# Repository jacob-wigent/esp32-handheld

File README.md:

# ESP32-S3 Handheld Game Console
Handheld game console powered by an ESP32-S3, featuring a custom LED matrix display and a variety of inputs.

ESP32-S3
2020 NeoPixels (WS2812B)

10/10
- added through-hole power JST connector on display board

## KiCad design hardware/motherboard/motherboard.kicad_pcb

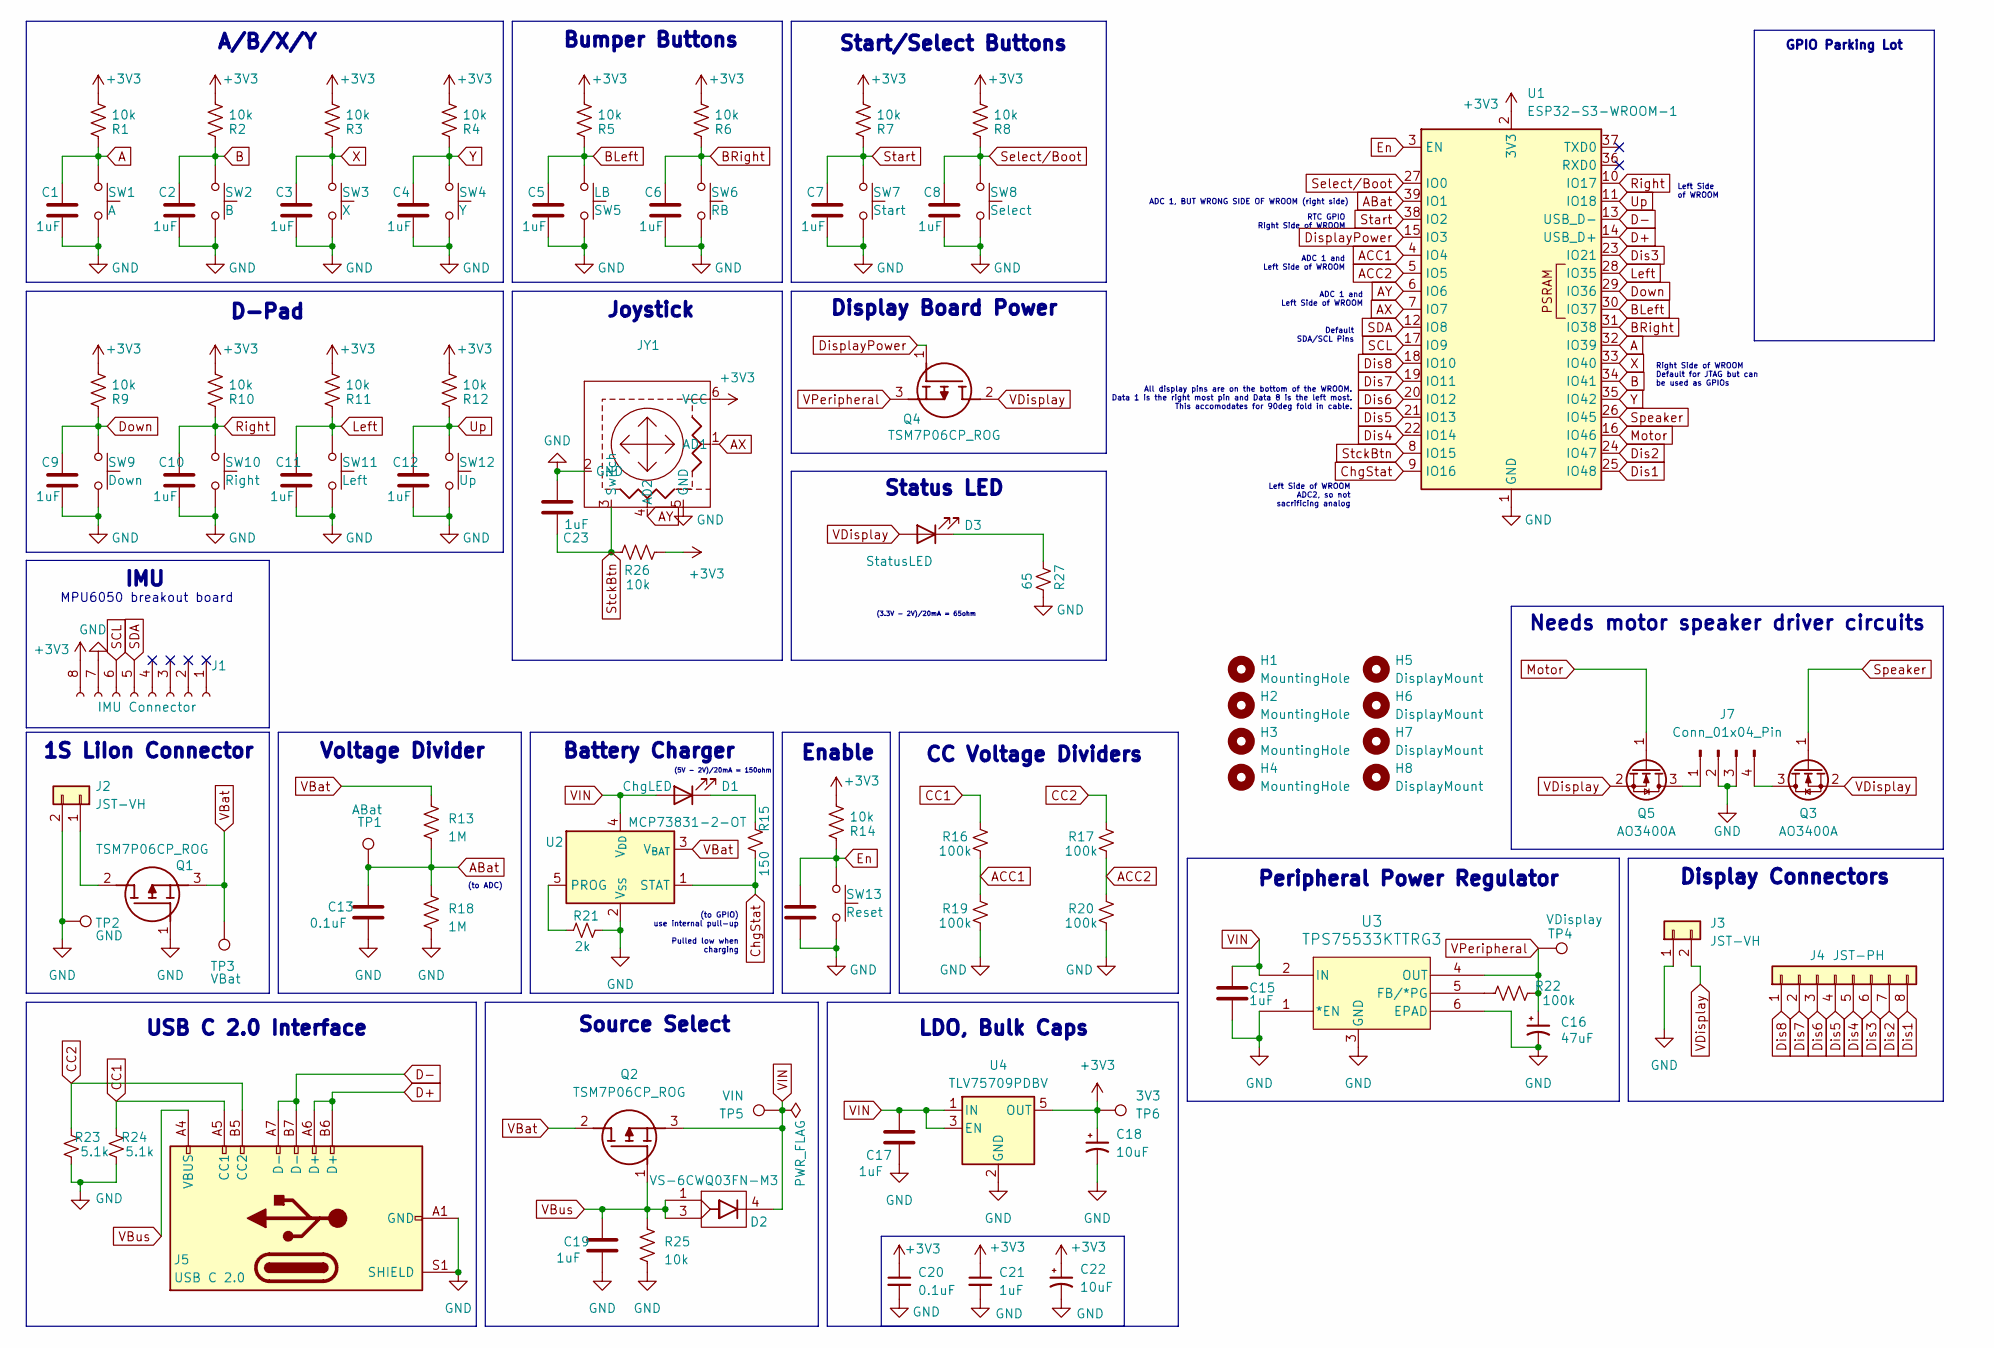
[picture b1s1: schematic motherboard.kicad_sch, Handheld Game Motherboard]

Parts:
C1, C2, C3, C4, C5, C6, C7, C8, C9, C10, C11, C12, C14, C15, C17, C19, C21, C23: 1uF; C_0805_2012Metric_Pad1.18x1.45mm_HandSolder
C13, C20: 0.1uF; C_0805_2012Metric_Pad1.18x1.45mm_HandSolder
C16: 47uF; CP_EIA-7343-31_Kemet-D
C18, C22: 10uF; C_0805_2012Metric_Pad1.18x1.45mm_HandSolder
D1: ChgLED; LED_1206_3216Metric_Pad1.42x1.75mm_HandSolder
D2: VS-6CWQ03FN-M3; DPAK_Q03FN-M3_VIS; Mouser Part Number 78-VS-6CWQ03FN-M3
D3: StatusLED; LED_1206_3216Metric_Pad1.42x1.75mm_HandSolder
H1, H2, H3, H4: MountingHole; MountingHole_3.2mm_M3_Pad
H5, H6, H7, H8: DisplayMount; MountingHole_3.2mm_M3_Pad
J1: IMU Connector; PinHeader_1x08_P2.54mm_Vertical
J2, J3: JST-VH; JST_VH_B2PS-VH_1x02_P3.96mm_Horizontal
J4: JST-PH; JST_PH_S8B-PH-K_1x08_P2.00mm_Horizontal
J5: USB C 2.0; USB_C_Receptacle_G-Switch_GT-USB-7010ASV
J7: Conn_01x04_Pin; JST_PH_S4B-PH-K_1x04_P2.00mm_Horizontal
JY1: Adafruit_Joycon
Q1, Q2, Q4: TSM7P06CP_ROG; TRANS_TSM7P06CP_ROG; Mouser Part Number 821-TSM7P06CPROG
Q3, Q5: AO3400A; SOT-23
R1, R2, R3, R4, R5, R6, R7, R8, R9, R10, R11, R12, R14, R25, R26: 10k; R_0805_2012Metric_Pad1.20x1.40mm_HandSolder
R13, R18: 1M; R_0805_2012Metric_Pad1.20x1.40mm_HandSolder
R15: 150; R_0805_2012Metric_Pad1.20x1.40mm_HandSolder
R16, R17, R19, R20, R22: 100k; R_0805_2012Metric_Pad1.20x1.40mm_HandSolder
R21: 2k; R_0805_2012Metric_Pad1.20x1.40mm_HandSolder
R23, R24: 5.1k; R_0805_2012Metric_Pad1.20x1.40mm_HandSolder
R27: 65; R_0805_2012Metric_Pad1.20x1.40mm_HandSolder
SW1: A; SW_PUSH_6mm
SW2: B; SW_PUSH_6mm
SW3: X; SW_PUSH_6mm
SW4: Y; SW_PUSH_6mm
SW5: LB; SW_Tactile_SPST_Angled_PTS645Vx58-2LFS
SW6: RB; SW_Tactile_SPST_Angled_PTS645Vx58-2LFS
SW7: Start; SW_PUSH_6mm
SW8: Select; SW_PUSH_6mm
SW9: Down; SW_PUSH_6mm
SW10: Right; SW_PUSH_6mm
SW11: Left; SW_PUSH_6mm
SW12: Up; SW_PUSH_6mm
SW13: Reset; SW_SPST_CK_RS282G05A3
TP1: ABat; TestPoint_Pad_D1.5mm
TP2: GND; TestPoint_Pad_D1.5mm
TP3: VBat; TestPoint_Pad_D1.5mm
TP4: VDisplay; TestPoint_Pad_D1.5mm
TP5: VIN; TestPoint_Pad_D1.5mm
TP6: 3V3; TestPoint_Pad_D1.5mm
U1: ESP32-S3-WROOM-1
U2: MCP73831-2-OT; SOT-23-5
U3: TPS75533KTTRG3; KTT5_6P22X6P86
U4: TLV75709PDBV; SOT-23-5

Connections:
+3V3: C18.1, C20.1, C21.1, C22.1, J1.8, JY1.6 (VCC), R1.2, R2.2, R3.2, R4.2, R5.2, R6.2, R7.2, R8.2, R9.2, R10.2, R11.2, R12.2, R14.2, R26.1, TP6.1, U1.2 (3V3), U4.5 (OUT)
A: C1.1, R1.1, SW1.1, U1.32 (IO39)
ABat: C13.1, R13.2, R18.1, TP1.1, U1.39 (IO1)
ACC1: R16.1, R19.2, U1.4 (IO4)
ACC2: R17.1, R20.2, U1.5 (IO5)
AX: JY1.1 (AD1), U1.7 (IO7)
AY: JY1.4 (AD2), U1.6 (IO6)
B: C2.1, R2.1, SW2.1, U1.34 (IO41)
BLeft: C5.1, R5.1, SW5.2, U1.30 (IO37)
BRight: C6.1, R6.1, SW6.1, U1.31 (IO38)
CC1: J5.A5 (CC1), R16.2, R24.2
CC2: J5.B5 (CC2), R17.2, R23.2
ChgStat: R15.1, U1.9 (IO16), U2.1 (STAT)
D+: J5.A6 (D+), J5.B6 (D+), U1.14 (USB_D+)
D-: J5.A7 (D-), J5.B7 (D-), U1.13 (USB_D-)
Dis1: J4.8, U1.25 (IO48)
Dis2: J4.7, U1.24 (IO47)
Dis3: J4.6, U1.23 (IO21)
Dis4: J4.5, U1.22 (IO14)
Dis5: J4.4, U1.21 (IO13)
Dis6: J4.3, U1.20 (IO12)
Dis7: J4.2, U1.19 (IO11)
Dis8: J4.1, U1.18 (IO10)
Down: C9.1, R9.1, SW9.1, U1.29 (IO36)
En: C14.1, R14.1, SW13.1, U1.3 (EN)
Left: C11.1, R11.1, SW11.1, U1.28 (IO35)
Motor: Q5.1 (G), U1.16 (IO46)
unnamed: D1.1 (K), R15.2
unnamed: D3.1 (K), R27.2
unnamed: J2.1, Q1.2 (D)
unnamed 30: J7.1, Q5.3 (D); also elsewhere on the board
unnamed 31: J7.4, Q3.3 (D); also elsewhere on the board
unnamed: R21.1, U2.5 (PROG)
unnamed: R22.1, U3.5 (FB/*PG)
Right: C10.1, R10.1, SW10.1, U1.10 (IO17)
SCL: J1.6, U1.17 (IO9)
SDA: J1.5, U1.12 (IO8)
Select/Boot: C8.1, R8.1, SW8.1, U1.27 (IO0)
Speaker: Q3.1 (G), U1.26 (IO45)
Start: C7.1, R7.1, SW7.1, U1.38 (IO2)
StckBtn: C23.2, JY1.3 (Switch), R26.2, U1.8 (IO15)
Up: C12.1, R12.1, SW12.1, U1.11 (IO18)
VBat: Q1.3 (S), Q2.2 (D), R13.1, TP3.1, U2.3 (V_{BAT})
VBus: C19.1, D2.1, D2.3, J5.A4 (VBUS), J5.A9 (VBUS), J5.B4 (VBUS), J5.B9 (VBUS), Q2.1 (G), R25.1
VIN: C15.1, C17.1, D1.2 (A), D2.4, Q2.3 (S), TP5.1, U2.4 (V_{DD}), U3.2 (IN), U4.1 (IN), U4.3 (EN)
X: C3.1, R3.1, SW3.1, U1.33 (IO40)
Y: C4.1, R4.1, SW4.1, U1.35 (IO42)

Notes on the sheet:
(to GPIO) use internal pull-up Pulled low when charging
LDO, Bulk Caps
Left Side of WROOM
Bumper Buttons
Needs motor speaker driver circuits
Display Connectors
ADC 1 and Left Side of WROOM
Start/Select Buttons
USB C 2.0 Interface
1S LiIon Connector
CC Voltage Dividers
Right Side of WROOM Default for JTAG but can be used as GPIOs
Peripheral Power Regulator
Voltage Divider
D-Pad
(5V - 2V)/20mA = 150ohm
Source Select
IMU
(3.3V - 2V)/20mA = 65ohm
A/B/X/Y
All display pins are on the bottom of the WROOM. Data 1 is the right most pin and Data 8 is the left most. This accomodates for 90deg fold in cable.
MPU6050 breakout board
ADC 1, BUT WRONG SIDE OF WROOM (right side)
RTC GPIO Right Side of WROOM
Enable
Battery Charger
Joystick
Status LED
GPIO Parking Lot
Left Side of WROOM ADC2, so not sacrificing analog
(to ADC)
Default SDA/SCL Pins
Display Board Power

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
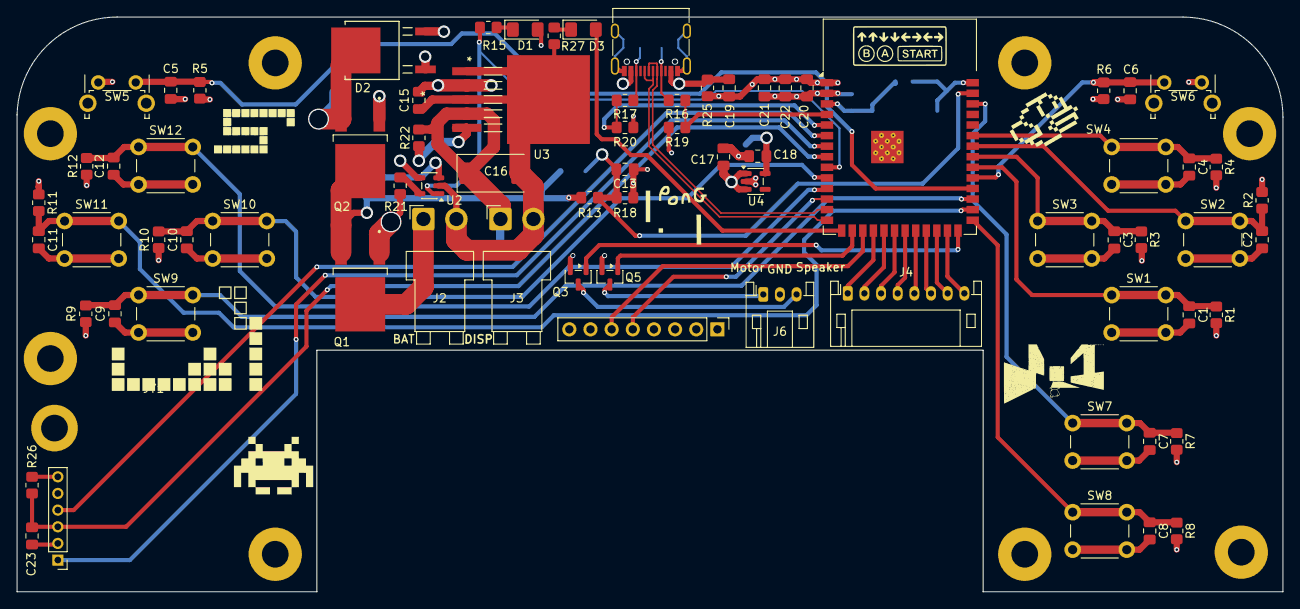
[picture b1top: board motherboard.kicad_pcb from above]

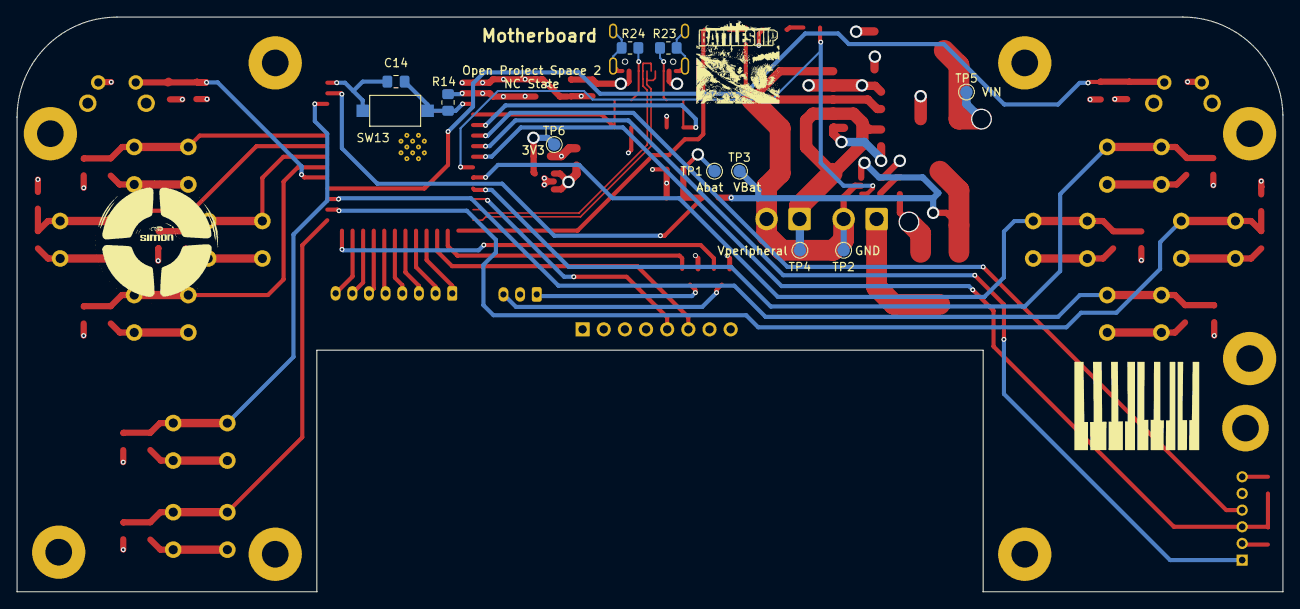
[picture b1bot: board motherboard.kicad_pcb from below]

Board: 4 copper layers, 152.0 x 69.0 mm, 95 parts (11 on the bottom side), 50 nets.

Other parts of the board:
J6: Conn_01x03_Pin; JST_PH_S3B-PH-K_1x03_P2.00mm_Horizontal

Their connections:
unnamed 30: J6.1; also elsewhere on the board
unnamed 31: J6.3; also elsewhere on the board

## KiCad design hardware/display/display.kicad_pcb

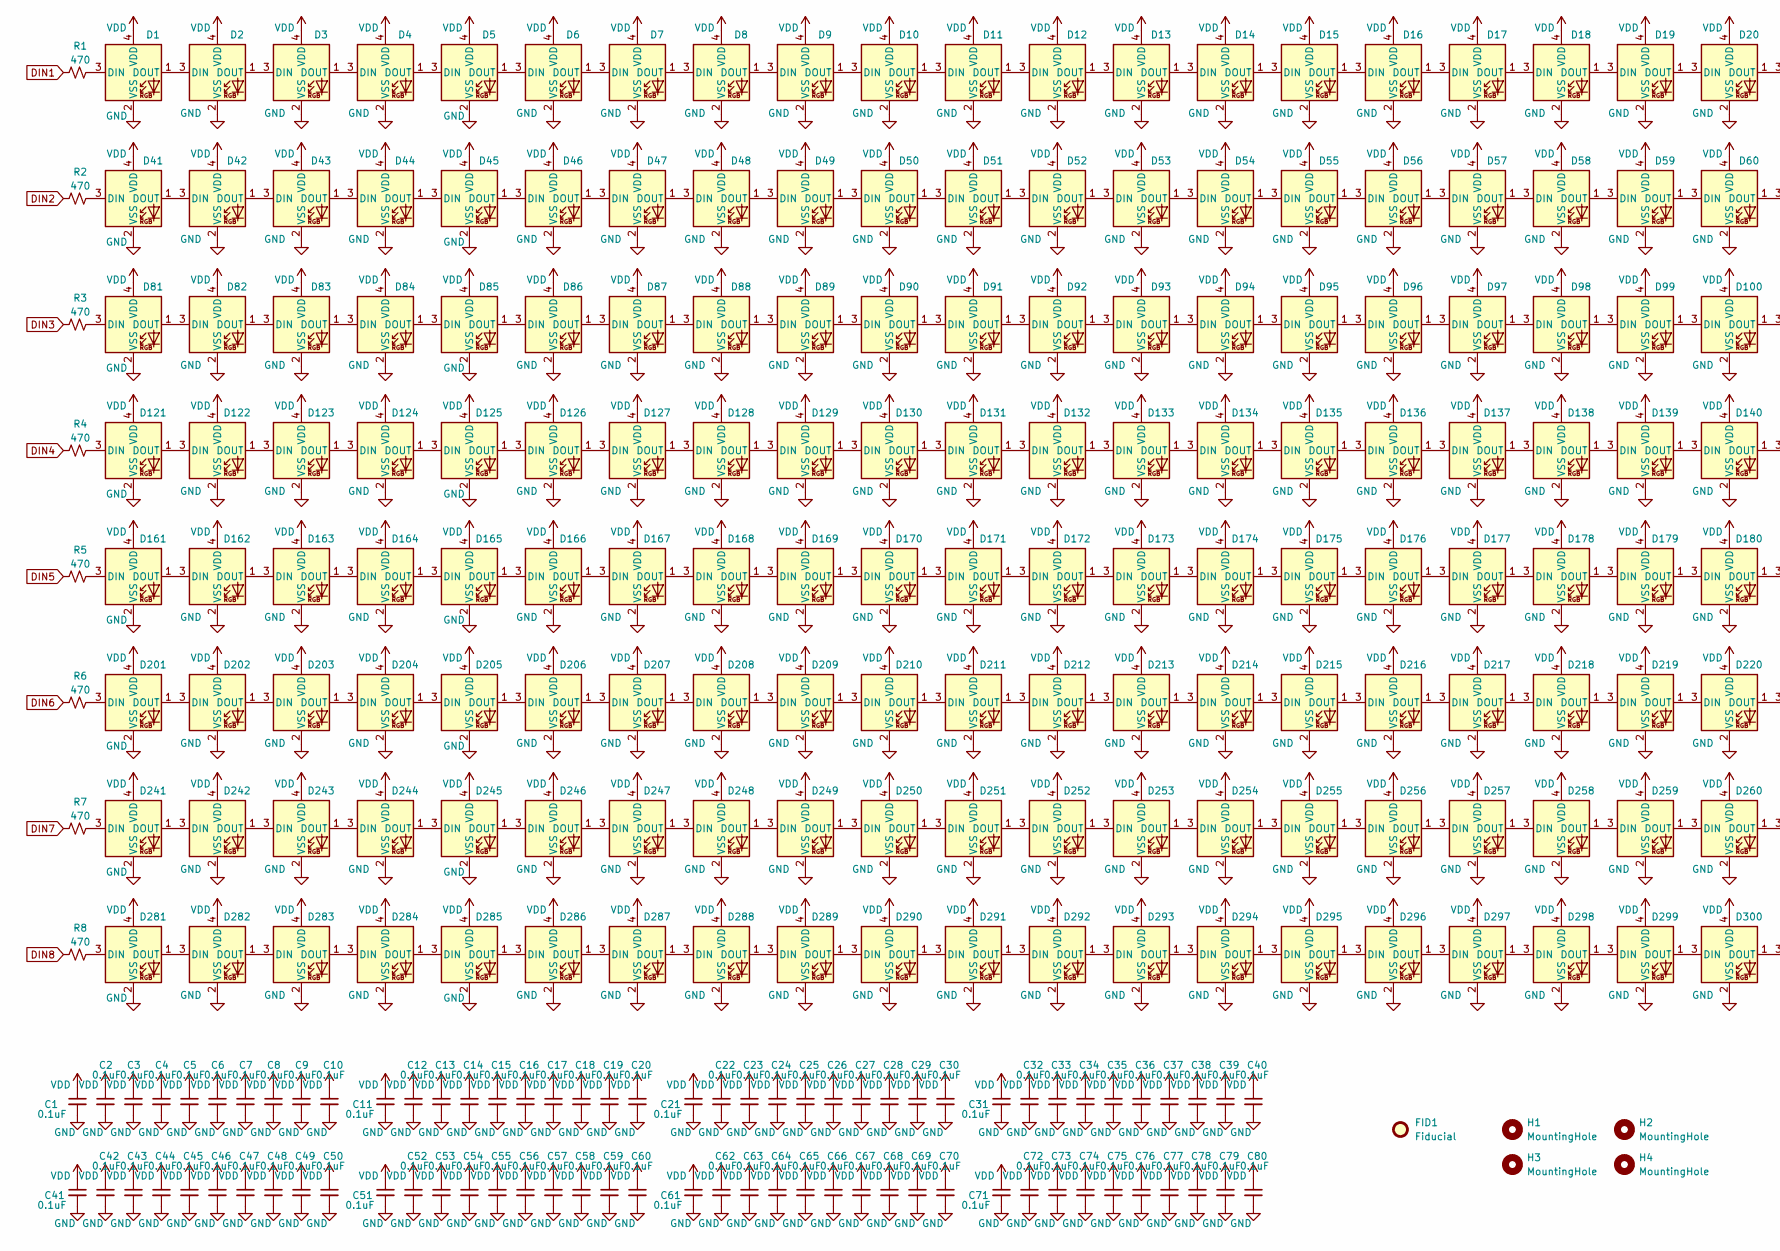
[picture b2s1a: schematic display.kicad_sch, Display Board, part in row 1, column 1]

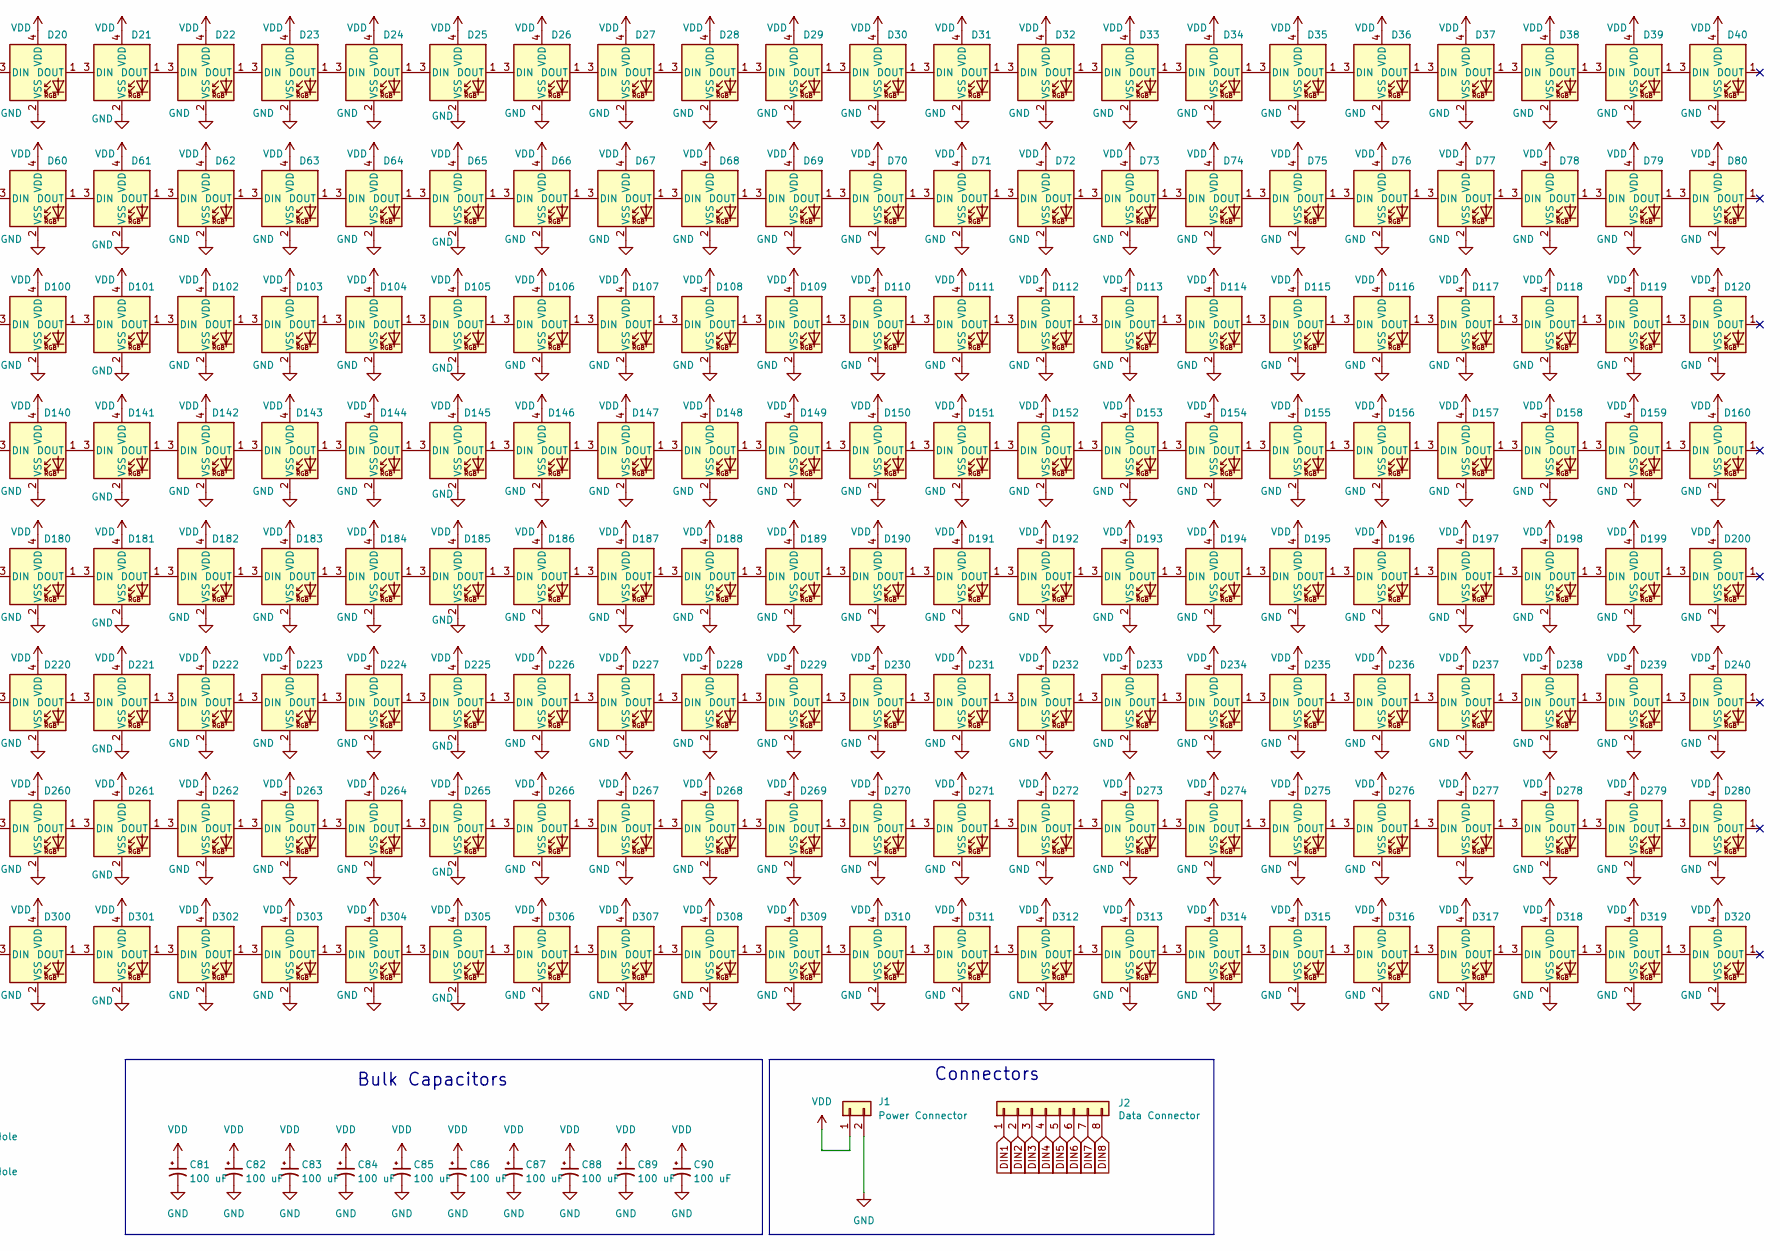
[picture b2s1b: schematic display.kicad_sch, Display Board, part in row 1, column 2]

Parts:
C1, C2, C3, C4, C5, C6, C7, C8, C9, C10, C11, C12, C13, C14, C15, C16, C17, C18, C19, C20, C21, C22, C23, C24, C25, C26, C27, C28, C29, C30, C31, C32, C33, C34, C35, C36, C37, C38, C39, C40, C41, C42, C43, C44, C45, C46, C47, C48, C49, C50, C51, C52, C53, C54, C55, C56, C57, C58, C59, C60, C61, C62, C63, C64, C65, C66, C67, C68, C69, C70, C71, C72, C73, C74, C75, C76, C77, C78, C79, C80: 0.1uF; C_0402_1005Metric_Pad0.74x0.62mm_HandSolder
C81, C82, C83, C84, C85, C86, C87, C88, C89, C90: 100 uF; CAP_TAJ-D- 2917-S_AVX_NO_RESTRICTION
D1, D2, D3, D4, D5, D6, D7, D8, D9, D10, D11, D12, D13, D14, D15, D16, D17, D18, D19, D20, D21, D22, D23, D24, D25, D26, D27, D28, D29, D30, D31, D32, D33, D34, D35, D36, D37, D38, D39, D40, D41, D42, D43, D44, D45, D46, D47, D48, D49, D50, D51, D52, D53, D54, D55, D56, D57, D58, D59, D60, D61, D62, D63, D64, D65, D66, D67, D68, D69, D70, D71, D72, D73, D74, D75, D76, D77, D78, D79, D80, D81, D82, D83, D84, D85, D86, D87, D88, D89, D90, D91, D92, D93, D94, D95, D96, D97, D98, D99, D100, D101, D102, D103, D104, D105, D106, D107, D108, D109, D110, D111, D112, D113, D114, D115, D116, D117, D118, D119, D120, D121, D122, D123, D124, D125, D126, D127, D128, D129, D130, D131, D132, D133, D134, D135, D136, D137, D138, D139, D140, D141, D142, D143, D144, D145, D146, D147, D148, D149, D150, D151, D152, D153, D154, D155, D156, D157, D158, D159, D160, D161, D162, D163, D164, D165, D166, D167, D168, D169, D170, D171, D172, D173, D174, D175, D176, D177, D178, D179, D180, D181, D182, D183, D184, D185, D186, D187, D188, D189, D190, D191, D192, D193, D194, D195, D196, D197, D198, D199, D200, D201, D202, D203, D204, D205, D206, D207, D208, D209, D210, D211, D212, D213, D214, D215, D216, D217, D218, D219, D220, D221, D222, D223, D224, D225, D226, D227, D228, D229, D230, D231, D232, D233, D234, D235, D236, D237, D238, D239, D240, D241, D242, D243, D244, D245, D246, D247, D248, D249, D250, D251, D252, D253, D254, D255, D256, D257, D258, D259, D260, D261, D262, D263, D264, D265, D266, D267, D268, D269, D270, D271, D272, D273, D274, D275, D276, D277, D278, D279, D280, D281, D282, D283, D284, D285, D286, D287, D288, D289, D290, D291, D292, D293, D294, D295, D296, D297, D298, D299, D300, D301, D302, D303, D304, D305, D306, D307, D308, D309, D310, D311, D312, D313, D314, D315, D316, D317, D318, D319, D320: WS2812B-2020; LED_WS2812B-2020_PLCC4_2.0x2.0mm
FID1: Fiducial; Fiducial_1mm_Mask2mm
H1, H2, H3, H4: MountingHole; MountingHole_3.2mm_M3_Pad
J1: Power Connector; JST_VH_B2PS-VH_1x02_P3.96mm_Horizontal
J2: Data Connector; JST_PH_S8B-PH-K_1x08_P2.00mm_Horizontal
R1, R2, R3, R4, R5, R6, R7, R8: 470; R_0603_1608Metric_Pad0.98x0.95mm_HandSolder

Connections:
DIN1: J2.1, R1.1
DIN2: J2.2, R2.1
DIN3: J2.3, R3.1
DIN4: J2.4, R4.1
DIN5: J2.5, R5.1
DIN6: J2.6, R6.1
DIN7: J2.7, R7.1
DIN8: J2.8, R8.1
GND: C1.2, C2.2, C3.2, C4.2, C5.2, C6.2, C7.2, C8.2, C9.2, C10.2, C11.2, C12.2, C13.2, C14.2, C15.2, C16.2, C17.2, C18.2, C19.2, C20.2, C21.2, C22.2, C23.2, C24.2, C25.2, C26.2, C27.2, C28.2, C29.2, C30.2, C31.2, C32.2, C33.2, C34.2, C35.2, C36.2, C37.2, C38.2, C39.2, C40.2, C41.2, C42.2, C43.2, C44.2, C45.2, C46.2, C47.2, C48.2, C49.2, C50.2, C51.2, C52.2, C53.2, C54.2, C55.2, C56.2, C57.2, C58.2, C59.2, C60.2, C61.2, C62.2, C63.2, C64.2, C65.2, C66.2, C67.2, C68.2, C69.2, C70.2, C71.2, C72.2, C73.2, C74.2, C75.2, C76.2, C77.2, C78.2, C79.2, C80.2, C81.2, C82.2, C83.2, C84.2, C85.2, C86.2, C87.2, C88.2, C89.2, C90.2, D1.2 (VSS), D2.2 (VSS), D3.2 (VSS), D4.2 (VSS), D5.2 (VSS), D6.2 (VSS), D7.2 (VSS), D8.2 (VSS), D9.2 (VSS), D10.2 (VSS), D11.2 (VSS), D12.2 (VSS), D13.2 (VSS), D14.2 (VSS), D15.2 (VSS), D16.2 (VSS), D17.2 (VSS), D18.2 (VSS), D19.2 (VSS), D20.2 (VSS), D21.2 (VSS), D22.2 (VSS), D23.2 (VSS), D24.2 (VSS), D25.2 (VSS), D26.2 (VSS), D27.2 (VSS), D28.2 (VSS), D29.2 (VSS), D30.2 (VSS), D31.2 (VSS), D32.2 (VSS), D33.2 (VSS), D34.2 (VSS), D35.2 (VSS), D36.2 (VSS), D37.2 (VSS), D38.2 (VSS), D39.2 (VSS), D40.2 (VSS), D41.2 (VSS), D42.2 (VSS), D43.2 (VSS), D44.2 (VSS), D45.2 (VSS), D46.2 (VSS), D47.2 (VSS), D48.2 (VSS), D49.2 (VSS), D50.2 (VSS), D51.2 (VSS), D52.2 (VSS), D53.2 (VSS), D54.2 (VSS), D55.2 (VSS), D56.2 (VSS), D57.2 (VSS), D58.2 (VSS), D59.2 (VSS), D60.2 (VSS), D61.2 (VSS), D62.2 (VSS), D63.2 (VSS), D64.2 (VSS), D65.2 (VSS), D66.2 (VSS), D67.2 (VSS), D68.2 (VSS), D69.2 (VSS), D70.2 (VSS), D71.2 (VSS), D72.2 (VSS), D73.2 (VSS), D74.2 (VSS), D75.2 (VSS), D76.2 (VSS), D77.2 (VSS), D78.2 (VSS), D79.2 (VSS), D80.2 (VSS), D81.2 (VSS), D82.2 (VSS), D83.2 (VSS), D84.2 (VSS), D85.2 (VSS), D86.2 (VSS), D87.2 (VSS), D88.2 (VSS), D89.2 (VSS), D90.2 (VSS), D91.2 (VSS), D92.2 (VSS), D93.2 (VSS), D94.2 (VSS), D95.2 (VSS), D96.2 (VSS), D97.2 (VSS), D98.2 (VSS), D99.2 (VSS), D100.2 (VSS), D101.2 (VSS), D102.2 (VSS), D103.2 (VSS), D104.2 (VSS), D105.2 (VSS), D106.2 (VSS), D107.2 (VSS), D108.2 (VSS), D109.2 (VSS), D110.2 (VSS), D111.2 (VSS), D112.2 (VSS), D113.2 (VSS), D114.2 (VSS), D115.2 (VSS), D116.2 (VSS), D117.2 (VSS), D118.2 (VSS), D119.2 (VSS), D120.2 (VSS), D121.2 (VSS), D122.2 (VSS), D123.2 (VSS), D124.2 (VSS), D125.2 (VSS), D126.2 (VSS), D127.2 (VSS), D128.2 (VSS), D129.2 (VSS), D130.2 (VSS), D131.2 (VSS), D132.2 (VSS), D133.2 (VSS), D134.2 (VSS), D135.2 (VSS), D136.2 (VSS), D137.2 (VSS), D138.2 (VSS), D139.2 (VSS), D140.2 (VSS), D141.2 (VSS), D142.2 (VSS), D143.2 (VSS), D144.2 (VSS), D145.2 (VSS), D146.2 (VSS), D147.2 (VSS), D148.2 (VSS), D149.2 (VSS), D150.2 (VSS), D151.2 (VSS), D152.2 (VSS), D153.2 (VSS), D154.2 (VSS), D155.2 (VSS), D156.2 (VSS), D157.2 (VSS), D158.2 (VSS), D159.2 (VSS), D160.2 (VSS), D161.2 (VSS), D162.2 (VSS), D163.2 (VSS), D164.2 (VSS), D165.2 (VSS), D166.2 (VSS), D167.2 (VSS), D168.2 (VSS), D169.2 (VSS), D170.2 (VSS), D171.2 (VSS), D172.2 (VSS), D173.2 (VSS), D174.2 (VSS), D175.2 (VSS), D176.2 (VSS), D177.2 (VSS), D178.2 (VSS), D179.2 (VSS), D180.2 (VSS), D181.2 (VSS), D182.2 (VSS), D183.2 (VSS), D184.2 (VSS), D185.2 (VSS), D186.2 (VSS), D187.2 (VSS), D188.2 (VSS), D189.2 (VSS), D190.2 (VSS), D191.2 (VSS), D192.2 (VSS), D193.2 (VSS), D194.2 (VSS), D195.2 (VSS), D196.2 (VSS), D197.2 (VSS), D198.2 (VSS), D199.2 (VSS), D200.2 (VSS), D201.2 (VSS), D202.2 (VSS), D203.2 (VSS), D204.2 (VSS), D205.2 (VSS), D206.2 (VSS), D207.2 (VSS), D208.2 (VSS), D209.2 (VSS), D210.2 (VSS), D211.2 (VSS), D212.2 (VSS), D213.2 (VSS), D214.2 (VSS), D215.2 (VSS), D216.2 (VSS), D217.2 (VSS), D218.2 (VSS), D219.2 (VSS), D220.2 (VSS), D221.2 (VSS), D222.2 (VSS), D223.2 (VSS), D224.2 (VSS), D225.2 (VSS), D226.2 (VSS), D227.2 (VSS), D228.2 (VSS), D229.2 (VSS), D230.2 (VSS), D231.2 (VSS), D232.2 (VSS), D233.2 (VSS), D234.2 (VSS), D235.2 (VSS), D236.2 (VSS), D237.2 (VSS), D238.2 (VSS), D239.2 (VSS), D240.2 (VSS), D241.2 (VSS), D242.2 (VSS), D243.2 (VSS), D244.2 (VSS), D245.2 (VSS), D246.2 (VSS), D247.2 (VSS), D248.2 (VSS)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
unnamed: D1.3 (DIN), R1.2
unnamed: D1.1 (DOUT), D2.3 (DIN)
unnamed: D2.1 (DOUT), D3.3 (DIN)
unnamed: D3.1 (DOUT), D4.3 (DIN)
unnamed: D4.1 (DOUT), D5.3 (DIN)
unnamed: D5.1 (DOUT), D6.3 (DIN)
unnamed: D6.1 (DOUT), D7.3 (DIN)
unnamed: D7.1 (DOUT), D8.3 (DIN)
unnamed: D8.1 (DOUT), D9.3 (DIN)
unnamed: D9.1 (DOUT), D10.3 (DIN)
unnamed: D10.1 (DOUT), D11.3 (DIN)
unnamed: D11.1 (DOUT), D12.3 (DIN)
unnamed: D12.1 (DOUT), D13.3 (DIN)
unnamed: D13.1 (DOUT), D14.3 (DIN)
unnamed: D14.1 (DOUT), D15.3 (DIN)
unnamed: D15.1 (DOUT), D16.3 (DIN)
unnamed: D16.1 (DOUT), D17.3 (DIN)
unnamed: D17.1 (DOUT), D18.3 (DIN)
unnamed: D18.1 (DOUT), D19.3 (DIN)
unnamed: D19.1 (DOUT), D20.3 (DIN)
unnamed: D20.1 (DOUT), D21.3 (DIN)
unnamed: D21.1 (DOUT), D22.3 (DIN)
unnamed: D22.1 (DOUT), D23.3 (DIN)
unnamed: D23.1 (DOUT), D24.3 (DIN)
unnamed: D24.1 (DOUT), D25.3 (DIN)
unnamed: D25.1 (DOUT), D26.3 (DIN)
unnamed: D26.1 (DOUT), D27.3 (DIN)
unnamed: D27.1 (DOUT), D28.3 (DIN)
unnamed: D28.1 (DOUT), D29.3 (DIN)
unnamed: D29.1 (DOUT), D30.3 (DIN)
unnamed: D30.1 (DOUT), D31.3 (DIN)
unnamed: D31.1 (DOUT), D32.3 (DIN)
unnamed: D32.1 (DOUT), D33.3 (DIN)
unnamed: D33.1 (DOUT), D34.3 (DIN)
unnamed: D34.1 (DOUT), D35.3 (DIN)
unnamed: D35.1 (DOUT), D36.3 (DIN)
unnamed: D36.1 (DOUT), D37.3 (DIN)
unnamed: D37.1 (DOUT), D38.3 (DIN)
unnamed: D38.1 (DOUT), D39.3 (DIN)
unnamed: D39.1 (DOUT), D40.3 (DIN)
unnamed: D41.3 (DIN), R2.2
unnamed: D41.1 (DOUT), D42.3 (DIN)
unnamed: D42.1 (DOUT), D43.3 (DIN)
unnamed: D43.1 (DOUT), D44.3 (DIN)
unnamed: D44.1 (DOUT), D45.3 (DIN)
unnamed: D45.1 (DOUT), D46.3 (DIN)
unnamed: D46.1 (DOUT), D47.3 (DIN)
unnamed: D47.1 (DOUT), D48.3 (DIN)
unnamed: D48.1 (DOUT), D49.3 (DIN)
unnamed: D49.1 (DOUT), D50.3 (DIN)
unnamed: D50.1 (DOUT), D51.3 (DIN)
unnamed: D51.1 (DOUT), D52.3 (DIN)
unnamed: D52.1 (DOUT), D53.3 (DIN)
unnamed: D53.1 (DOUT), D54.3 (DIN)
unnamed: D54.1 (DOUT), D55.3 (DIN)
unnamed: D55.1 (DOUT), D56.3 (DIN)
unnamed: D56.1 (DOUT), D57.3 (DIN)
unnamed: D57.1 (DOUT), D58.3 (DIN)
unnamed: D58.1 (DOUT), D59.3 (DIN)
unnamed: D59.1 (DOUT), D60.3 (DIN)
unnamed: D60.1 (DOUT), D61.3 (DIN)
unnamed: D61.1 (DOUT), D62.3 (DIN)
unnamed: D62.1 (DOUT), D63.3 (DIN)
unnamed: D63.1 (DOUT), D64.3 (DIN)
unnamed: D64.1 (DOUT), D65.3 (DIN)
unnamed: D65.1 (DOUT), D66.3 (DIN)
unnamed: D66.1 (DOUT), D67.3 (DIN)
unnamed: D67.1 (DOUT), D68.3 (DIN)
unnamed: D68.1 (DOUT), D69.3 (DIN)
unnamed: D69.1 (DOUT), D70.3 (DIN)
unnamed: D70.1 (DOUT), D71.3 (DIN)
unnamed: D71.1 (DOUT), D72.3 (DIN)
unnamed: D72.1 (DOUT), D73.3 (DIN)
unnamed: D73.1 (DOUT), D74.3 (DIN)
unnamed: D74.1 (DOUT), D75.3 (DIN)
unnamed: D75.1 (DOUT), D76.3 (DIN)
unnamed: D76.1 (DOUT), D77.3 (DIN)
unnamed: D77.1 (DOUT), D78.3 (DIN)
unnamed: D78.1 (DOUT), D79.3 (DIN)
unnamed: D79.1 (DOUT), D80.3 (DIN)
unnamed: D81.3 (DIN), R3.2
unnamed: D81.1 (DOUT), D82.3 (DIN)
unnamed: D82.1 (DOUT), D83.3 (DIN)
unnamed: D83.1 (DOUT), D84.3 (DIN)
unnamed: D84.1 (DOUT), D85.3 (DIN)
unnamed: D85.1 (DOUT), D86.3 (DIN)
unnamed: D86.1 (DOUT), D87.3 (DIN)
unnamed: D87.1 (DOUT), D88.3 (DIN)
unnamed: D88.1 (DOUT), D89.3 (DIN)
unnamed: D89.1 (DOUT), D90.3 (DIN)
unnamed: D90.1 (DOUT), D91.3 (DIN)
unnamed: D91.1 (DOUT), D92.3 (DIN)
unnamed: D92.1 (DOUT), D93.3 (DIN)
unnamed: D93.1 (DOUT), D94.3 (DIN)
unnamed: D94.1 (DOUT), D95.3 (DIN)
unnamed: D95.1 (DOUT), D96.3 (DIN)
unnamed: D96.1 (DOUT), D97.3 (DIN)
unnamed: D97.1 (DOUT), D98.3 (DIN)
unnamed: D98.1 (DOUT), D99.3 (DIN)
unnamed: D99.1 (DOUT), D100.3 (DIN)
unnamed: D100.1 (DOUT), D101.3 (DIN)
unnamed: D101.1 (DOUT), D102.3 (DIN)
unnamed: D102.1 (DOUT), D103.3 (DIN)
unnamed: D103.1 (DOUT), D104.3 (DIN)
unnamed: D104.1 (DOUT), D105.3 (DIN)
unnamed: D105.1 (DOUT), D106.3 (DIN)
unnamed: D106.1 (DOUT), D107.3 (DIN)
unnamed: D107.1 (DOUT), D108.3 (DIN)
unnamed: D108.1 (DOUT), D109.3 (DIN)
unnamed: D109.1 (DOUT), D110.3 (DIN)
unnamed: D110.1 (DOUT), D111.3 (DIN)
unnamed: D111.1 (DOUT), D112.3 (DIN)
unnamed: D112.1 (DOUT), D113.3 (DIN)
unnamed: D113.1 (DOUT), D114.3 (DIN)
unnamed: D114.1 (DOUT), D115.3 (DIN)
unnamed: D115.1 (DOUT), D116.3 (DIN)
unnamed: D116.1 (DOUT), D117.3 (DIN)
unnamed: D117.1 (DOUT), D118.3 (DIN)
unnamed: D118.1 (DOUT), D119.3 (DIN)
unnamed: D119.1 (DOUT), D120.3 (DIN)
unnamed: D121.3 (DIN), R4.2
unnamed: D121.1 (DOUT), D122.3 (DIN)
unnamed: D122.1 (DOUT), D123.3 (DIN)
unnamed: D123.1 (DOUT), D124.3 (DIN)
unnamed: D124.1 (DOUT), D125.3 (DIN)
unnamed: D125.1 (DOUT), D126.3 (DIN)
unnamed: D126.1 (DOUT), D127.3 (DIN)
unnamed: D127.1 (DOUT), D128.3 (DIN)
unnamed: D128.1 (DOUT), D129.3 (DIN)
unnamed: D129.1 (DOUT), D130.3 (DIN)
unnamed: D130.1 (DOUT), D131.3 (DIN)
unnamed: D131.1 (DOUT), D132.3 (DIN)
unnamed: D132.1 (DOUT), D133.3 (DIN)
unnamed: D133.1 (DOUT), D134.3 (DIN)
unnamed: D134.1 (DOUT), D135.3 (DIN)
unnamed: D135.1 (DOUT), D136.3 (DIN)
unnamed: D136.1 (DOUT), D137.3 (DIN)
unnamed: D137.1 (DOUT), D138.3 (DIN)
unnamed: D138.1 (DOUT), D139.3 (DIN)
unnamed: D139.1 (DOUT), D140.3 (DIN)
unnamed: D140.1 (DOUT), D141.3 (DIN)
unnamed: D141.1 (DOUT), D142.3 (DIN)
unnamed: D142.1 (DOUT), D143.3 (DIN)
unnamed: D143.1 (DOUT), D144.3 (DIN)
unnamed: D144.1 (DOUT), D145.3 (DIN)
unnamed: D145.1 (DOUT), D146.3 (DIN)
unnamed: D146.1 (DOUT), D147.3 (DIN)
unnamed: D147.1 (DOUT), D148.3 (DIN)
unnamed: D148.1 (DOUT), D149.3 (DIN)
unnamed: D149.1 (DOUT), D150.3 (DIN)
unnamed: D150.1 (DOUT), D151.3 (DIN)
unnamed: D151.1 (DOUT), D152.3 (DIN)
unnamed: D152.1 (DOUT), D153.3 (DIN)
unnamed: D153.1 (DOUT), D154.3 (DIN)
unnamed: D154.1 (DOUT), D155.3 (DIN)
unnamed: D155.1 (DOUT), D156.3 (DIN)
unnamed: D156.1 (DOUT), D157.3 (DIN)
unnamed: D157.1 (DOUT), D158.3 (DIN)
unnamed: D158.1 (DOUT), D159.3 (DIN)
unnamed: D159.1 (DOUT), D160.3 (DIN)
unnamed: D161.3 (DIN), R5.2
unnamed: D161.1 (DOUT), D162.3 (DIN)
unnamed: D162.1 (DOUT), D163.3 (DIN)
unnamed: D163.1 (DOUT), D164.3 (DIN)
unnamed: D164.1 (DOUT), D165.3 (DIN)
unnamed: D165.1 (DOUT), D166.3 (DIN)
unnamed: D166.1 (DOUT), D167.3 (DIN)
unnamed: D167.1 (DOUT), D168.3 (DIN)
unnamed: D168.1 (DOUT), D169.3 (DIN)
unnamed: D169.1 (DOUT), D170.3 (DIN)
unnamed: D170.1 (DOUT), D171.3 (DIN)
unnamed: D171.1 (DOUT), D172.3 (DIN)
unnamed: D172.1 (DOUT), D173.3 (DIN)
unnamed: D173.1 (DOUT), D174.3 (DIN)
unnamed: D174.1 (DOUT), D175.3 (DIN)
unnamed: D175.1 (DOUT), D176.3 (DIN)
unnamed: D176.1 (DOUT), D177.3 (DIN)
unnamed: D177.1 (DOUT), D178.3 (DIN)
unnamed: D178.1 (DOUT), D179.3 (DIN)
unnamed: D179.1 (DOUT), D180.3 (DIN)
unnamed: D180.1 (DOUT), D181.3 (DIN)
unnamed: D181.1 (DOUT), D182.3 (DIN)
unnamed: D182.1 (DOUT), D183.3 (DIN)
unnamed: D183.1 (DOUT), D184.3 (DIN)
unnamed: D184.1 (DOUT), D185.3 (DIN)
unnamed: D185.1 (DOUT), D186.3 (DIN)
unnamed: D186.1 (DOUT), D187.3 (DIN)
unnamed: D187.1 (DOUT), D188.3 (DIN)
unnamed: D188.1 (DOUT), D189.3 (DIN)
unnamed: D189.1 (DOUT), D190.3 (DIN)
unnamed: D190.1 (DOUT), D191.3 (DIN)
unnamed: D191.1 (DOUT), D192.3 (DIN)
unnamed: D192.1 (DOUT), D193.3 (DIN)
unnamed: D193.1 (DOUT), D194.3 (DIN)
unnamed: D194.1 (DOUT), D195.3 (DIN)
unnamed: D195.1 (DOUT), D196.3 (DIN)
unnamed: D196.1 (DOUT), D197.3 (DIN)
unnamed: D197.1 (DOUT), D198.3 (DIN)
unnamed: D198.1 (DOUT), D199.3 (DIN)
unnamed: D199.1 (DOUT), D200.3 (DIN)
unnamed: D201.3 (DIN), R6.2
unnamed: D201.1 (DOUT), D202.3 (DIN)
unnamed: D202.1 (DOUT), D203.3 (DIN)
unnamed: D203.1 (DOUT), D204.3 (DIN)
unnamed: D204.1 (DOUT), D205.3 (DIN)
unnamed: D205.1 (DOUT), D206.3 (DIN)
unnamed: D206.1 (DOUT), D207.3 (DIN)
unnamed: D207.1 (DOUT), D208.3 (DIN)
unnamed: D208.1 (DOUT), D209.3 (DIN)
unnamed: D209.1 (DOUT), D210.3 (DIN)
unnamed: D210.1 (DOUT), D211.3 (DIN)
unnamed: D211.1 (DOUT), D212.3 (DIN)
unnamed: D212.1 (DOUT), D213.3 (DIN)
unnamed: D213.1 (DOUT), D214.3 (DIN)
unnamed: D214.1 (DOUT), D215.3 (DIN)
unnamed: D215.1 (DOUT), D216.3 (DIN)
unnamed: D216.1 (DOUT), D217.3 (DIN)
unnamed: D217.1 (DOUT), D218.3 (DIN)
unnamed: D218.1 (DOUT), D219.3 (DIN)
unnamed: D219.1 (DOUT), D220.3 (DIN)
unnamed: D220.1 (DOUT), D221.3 (DIN)
unnamed: D221.1 (DOUT), D222.3 (DIN)
unnamed: D222.1 (DOUT), D223.3 (DIN)
unnamed: D223.1 (DOUT), D224.3 (DIN)
unnamed: D224.1 (DOUT), D225.3 (DIN)
unnamed: D225.1 (DOUT), D226.3 (DIN)
unnamed: D226.1 (DOUT), D227.3 (DIN)
unnamed: D227.1 (DOUT), D228.3 (DIN)
unnamed: D228.1 (DOUT), D229.3 (DIN)
unnamed: D229.1 (DOUT), D230.3 (DIN)
unnamed: D230.1 (DOUT), D231.3 (DIN)
unnamed: D231.1 (DOUT), D232.3 (DIN)
unnamed: D232.1 (DOUT), D233.3 (DIN)
unnamed: D233.1 (DOUT), D234.3 (DIN)
unnamed: D234.1 (DOUT), D235.3 (DIN)
unnamed: D235.1 (DOUT), D236.3 (DIN)
unnamed: D236.1 (DOUT), D237.3 (DIN)
unnamed: D237.1 (DOUT), D238.3 (DIN)
unnamed: D238.1 (DOUT), D239.3 (DIN)
unnamed: D239.1 (DOUT), D240.3 (DIN)
unnamed: D241.3 (DIN), R7.2
unnamed: D241.1 (DOUT), D242.3 (DIN)
unnamed: D242.1 (DOUT), D243.3 (DIN)
unnamed: D243.1 (DOUT), D244.3 (DIN)
unnamed: D244.1 (DOUT), D245.3 (DIN)
unnamed: D245.1 (DOUT), D246.3 (DIN)
unnamed: D246.1 (DOUT), D247.3 (DIN)
unnamed: D247.1 (DOUT), D248.3 (DIN)
unnamed: D248.1 (DOUT), D249.3 (DIN)
unnamed: D249.1 (DOUT), D250.3 (DIN)
unnamed: D250.1 (DOUT), D251.3 (DIN)
unnamed: D251.1 (DOUT), D252.3 (DIN)
unnamed: D252.1 (DOUT), D253.3 (DIN)
unnamed: D253.1 (DOUT), D254.3 (DIN)
unnamed: D254.1 (DOUT), D255.3 (DIN)
unnamed: D255.1 (DOUT), D256.3 (DIN)
unnamed: D256.1 (DOUT), D257.3 (DIN)
unnamed: D257.1 (DOUT), D258.3 (DIN)
unnamed: D258.1 (DOUT), D259.3 (DIN)
unnamed: D259.1 (DOUT), D260.3 (DIN)
unnamed: D260.1 (DOUT), D261.3 (DIN)
unnamed: D261.1 (DOUT), D262.3 (DIN)
unnamed: D262.1 (DOUT), D263.3 (DIN)
unnamed: D263.1 (DOUT), D264.3 (DIN)
unnamed: D264.1 (DOUT), D265.3 (DIN)
unnamed: D265.1 (DOUT), D266.3 (DIN)
unnamed: D266.1 (DOUT), D267.3 (DIN)
unnamed: D267.1 (DOUT), D268.3 (DIN)
unnamed: D268.1 (DOUT), D269.3 (DIN)
unnamed: D269.1 (DOUT), D270.3 (DIN)
unnamed: D270.1 (DOUT), D271.3 (DIN)
unnamed: D271.1 (DOUT), D272.3 (DIN)
unnamed: D272.1 (DOUT), D273.3 (DIN)
unnamed: D273.1 (DOUT), D274.3 (DIN)
unnamed: D274.1 (DOUT), D275.3 (DIN)
unnamed: D275.1 (DOUT), D276.3 (DIN)
unnamed: D276.1 (DOUT), D277.3 (DIN)
unnamed: D277.1 (DOUT), D278.3 (DIN)
unnamed: D278.1 (DOUT), D279.3 (DIN)
unnamed: D279.1 (DOUT), D280.3 (DIN)
unnamed: D281.3 (DIN), R8.2
unnamed: D281.1 (DOUT), D282.3 (DIN)
unnamed: D282.1 (DOUT), D283.3 (DIN)
unnamed: D283.1 (DOUT), D284.3 (DIN)
unnamed: D284.1 (DOUT), D285.3 (DIN)
unnamed: D285.1 (DOUT), D286.3 (DIN)
unnamed: D286.1 (DOUT), D287.3 (DIN)
unnamed: D287.1 (DOUT), D288.3 (DIN)
unnamed: D288.1 (DOUT), D289.3 (DIN)
unnamed: D289.1 (DOUT), D290.3 (DIN)
unnamed: D290.1 (DOUT), D291.3 (DIN)
unnamed: D291.1 (DOUT), D292.3 (DIN)
unnamed: D292.1 (DOUT), D293.3 (DIN)
unnamed: D293.1 (DOUT), D294.3 (DIN)
unnamed: D294.1 (DOUT), D295.3 (DIN)
unnamed: D295.1 (DOUT), D296.3 (DIN)
unnamed: D296.1 (DOUT), D297.3 (DIN)
unnamed: D297.1 (DOUT), D298.3 (DIN)
unnamed: D298.1 (DOUT), D299.3 (DIN)
unnamed: D299.1 (DOUT), D300.3 (DIN)
unnamed: D300.1 (DOUT), D301.3 (DIN)
unnamed: D301.1 (DOUT), D302.3 (DIN)
unnamed: D302.1 (DOUT), D303.3 (DIN)
unnamed: D303.1 (DOUT), D304.3 (DIN)
unnamed: D304.1 (DOUT), D305.3 (DIN)
unnamed: D305.1 (DOUT), D306.3 (DIN)
unnamed: D306.1 (DOUT), D307.3 (DIN)
unnamed: D307.1 (DOUT), D308.3 (DIN)
unnamed: D308.1 (DOUT), D309.3 (DIN)
unnamed: D309.1 (DOUT), D310.3 (DIN)
unnamed: D310.1 (DOUT), D311.3 (DIN)
unnamed: D311.1 (DOUT), D312.3 (DIN)
unnamed: D312.1 (DOUT), D313.3 (DIN)
unnamed: D313.1 (DOUT), D314.3 (DIN)
unnamed: D314.1 (DOUT), D315.3 (DIN)
unnamed: D315.1 (DOUT), D316.3 (DIN)
unnamed: D316.1 (DOUT), D317.3 (DIN)
unnamed: D317.1 (DOUT), D318.3 (DIN)
unnamed: D318.1 (DOUT), D319.3 (DIN)
unnamed: D319.1 (DOUT), D320.3 (DIN)
VDD: C1.1, C2.1, C3.1, C4.1, C5.1, C6.1, C7.1, C8.1, C9.1, C10.1, C11.1, C12.1, C13.1, C14.1, C15.1, C16.1, C17.1, C18.1, C19.1, C20.1, C21.1, C22.1, C23.1, C24.1, C25.1, C26.1, C27.1, C28.1, C29.1, C30.1, C31.1, C32.1, C33.1, C34.1, C35.1, C36.1, C37.1, C38.1, C39.1, C40.1, C41.1, C42.1, C43.1, C44.1, C45.1, C46.1, C47.1, C48.1, C49.1, C50.1, C51.1, C52.1, C53.1, C54.1, C55.1, C56.1, C57.1, C58.1, C59.1, C60.1, C61.1, C62.1, C63.1, C64.1, C65.1, C66.1, C67.1, C68.1, C69.1, C70.1, C71.1, C72.1, C73.1, C74.1, C75.1, C76.1, C77.1, C78.1, C79.1, C80.1, C81.1, C82.1, C83.1, C84.1, C85.1, C86.1, C87.1, C88.1, C89.1, C90.1, D1.4 (VDD), D2.4 (VDD), D3.4 (VDD), D4.4 (VDD), D5.4 (VDD), D6.4 (VDD), D7.4 (VDD), D8.4 (VDD), D9.4 (VDD), D10.4 (VDD), D11.4 (VDD), D12.4 (VDD), D13.4 (VDD), D14.4 (VDD), D15.4 (VDD), D16.4 (VDD), D17.4 (VDD), D18.4 (VDD), D19.4 (VDD), D20.4 (VDD), D21.4 (VDD), D22.4 (VDD), D23.4 (VDD), D24.4 (VDD), D25.4 (VDD), D26.4 (VDD), D27.4 (VDD), D28.4 (VDD), D29.4 (VDD), D30.4 (VDD), D31.4 (VDD), D32.4 (VDD), D33.4 (VDD), D34.4 (VDD), D35.4 (VDD), D36.4 (VDD), D37.4 (VDD), D38.4 (VDD), D39.4 (VDD), D40.4 (VDD), D41.4 (VDD), D42.4 (VDD), D43.4 (VDD), D44.4 (VDD), D45.4 (VDD), D46.4 (VDD), D47.4 (VDD), D48.4 (VDD), D49.4 (VDD), D50.4 (VDD), D51.4 (VDD), D52.4 (VDD), D53.4 (VDD), D54.4 (VDD), D55.4 (VDD), D56.4 (VDD), D57.4 (VDD), D58.4 (VDD), D59.4 (VDD), D60.4 (VDD), D61.4 (VDD), D62.4 (VDD), D63.4 (VDD), D64.4 (VDD), D65.4 (VDD), D66.4 (VDD), D67.4 (VDD), D68.4 (VDD), D69.4 (VDD), D70.4 (VDD), D71.4 (VDD), D72.4 (VDD), D73.4 (VDD), D74.4 (VDD), D75.4 (VDD), D76.4 (VDD), D77.4 (VDD), D78.4 (VDD), D79.4 (VDD), D80.4 (VDD), D81.4 (VDD), D82.4 (VDD), D83.4 (VDD), D84.4 (VDD), D85.4 (VDD), D86.4 (VDD), D87.4 (VDD), D88.4 (VDD), D89.4 (VDD), D90.4 (VDD), D91.4 (VDD), D92.4 (VDD), D93.4 (VDD), D94.4 (VDD), D95.4 (VDD), D96.4 (VDD), D97.4 (VDD), D98.4 (VDD), D99.4 (VDD), D100.4 (VDD), D101.4 (VDD), D102.4 (VDD), D103.4 (VDD), D104.4 (VDD), D105.4 (VDD), D106.4 (VDD), D107.4 (VDD), D108.4 (VDD), D109.4 (VDD), D110.4 (VDD), D111.4 (VDD), D112.4 (VDD), D113.4 (VDD), D114.4 (VDD), D115.4 (VDD), D116.4 (VDD), D117.4 (VDD), D118.4 (VDD), D119.4 (VDD), D120.4 (VDD), D121.4 (VDD), D122.4 (VDD), D123.4 (VDD), D124.4 (VDD), D125.4 (VDD), D126.4 (VDD), D127.4 (VDD), D128.4 (VDD), D129.4 (VDD), D130.4 (VDD), D131.4 (VDD), D132.4 (VDD), D133.4 (VDD), D134.4 (VDD), D135.4 (VDD), D136.4 (VDD), D137.4 (VDD), D138.4 (VDD), D139.4 (VDD), D140.4 (VDD), D141.4 (VDD), D142.4 (VDD), D143.4 (VDD), D144.4 (VDD), D145.4 (VDD), D146.4 (VDD), D147.4 (VDD), D148.4 (VDD), D149.4 (VDD), D150.4 (VDD), D151.4 (VDD), D152.4 (VDD), D153.4 (VDD), D154.4 (VDD), D155.4 (VDD), D156.4 (VDD), D157.4 (VDD), D158.4 (VDD), D159.4 (VDD), D160.4 (VDD), D161.4 (VDD), D162.4 (VDD), D163.4 (VDD), D164.4 (VDD), D165.4 (VDD), D166.4 (VDD), D167.4 (VDD), D168.4 (VDD), D169.4 (VDD), D170.4 (VDD), D171.4 (VDD), D172.4 (VDD), D173.4 (VDD), D174.4 (VDD), D175.4 (VDD), D176.4 (VDD), D177.4 (VDD), D178.4 (VDD), D179.4 (VDD), D180.4 (VDD), D181.4 (VDD), D182.4 (VDD), D183.4 (VDD), D184.4 (VDD), D185.4 (VDD), D186.4 (VDD), D187.4 (VDD), D188.4 (VDD), D189.4 (VDD), D190.4 (VDD), D191.4 (VDD), D192.4 (VDD), D193.4 (VDD), D194.4 (VDD), D195.4 (VDD), D196.4 (VDD), D197.4 (VDD), D198.4 (VDD), D199.4 (VDD), D200.4 (VDD), D201.4 (VDD), D202.4 (VDD), D203.4 (VDD), D204.4 (VDD), D205.4 (VDD), D206.4 (VDD), D207.4 (VDD), D208.4 (VDD), D209.4 (VDD), D210.4 (VDD), D211.4 (VDD), D212.4 (VDD), D213.4 (VDD), D214.4 (VDD), D215.4 (VDD), D216.4 (VDD), D217.4 (VDD), D218.4 (VDD), D219.4 (VDD), D220.4 (VDD), D221.4 (VDD), D222.4 (VDD), D223.4 (VDD), D224.4 (VDD), D225.4 (VDD), D226.4 (VDD), D227.4 (VDD), D228.4 (VDD), D229.4 (VDD), D230.4 (VDD), D231.4 (VDD), D232.4 (VDD), D233.4 (VDD), D234.4 (VDD), D235.4 (VDD), D236.4 (VDD), D237.4 (VDD), D238.4 (VDD), D239.4 (VDD), D240.4 (VDD), D241.4 (VDD), D242.4 (VDD), D243.4 (VDD), D244.4 (VDD), D245.4 (VDD), D246.4 (VDD), D247.4 (VDD), D248.4 (VDD)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

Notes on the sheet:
Bulk Capacitors
Connectors
